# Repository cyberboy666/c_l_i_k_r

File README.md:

# c_l_i_k_r
a [r_e_c_u_r](https://github.com/cyberboy666/r_e_c_u_r) video sampler extension circuit - custom keypad & midi controller

- this circuit is distributed by __UNDERSCORES__ - _an open video hardware label_ : it is available to purchase - as a pcb, kit or assembled unit - at [underscores.shop](https://underscores.shop/c_l_i_k_r/)
- the schematic for the circuit can be found [here](/hardware/schematic.pdf)
- the pcb gerber files for the lastest version can be found [here](/hardware/gerber_latest.zip)
- interactive BOM is [here](https://htmlpreview.github.io/?https://github.com/cyberboy666/c_l_i_k_r/blob/main/hardware/bom/ibom.html)
- consider [donating](https://opencollective.com/underscores) to the underscores project to help us continue creating for the commons
## description

__NOTE__ : _c_l_i_k_r is an extension circuit for my existing raspberry pi project [r_e_c_u_r](https://github.com/cyberboy666/r_e_c_u_r) - although this circuit will function as a stand alone midi+keypad controller it is mainly intended to be used with r_e_c_u_r_

This is a custom controller designed to operate the rpi video instrument r_e_c_u_r. It uses an arduino pro-micro to send key-presses and midi values to the pi over usb

- 20x tac-switches for discrete control
- 4x knobs + 4x cv inputs for continuous control
- firmware can be configured to send midi messages or keyboard presses

## demo video

### background

this is an extension circuit that aims to offer an alternative to using cheapo plastic numpads to control recur. when i first designed recur i decided to use [these](https://www.aliexpress.com/item/4000748567192.html) numpads from aliexpress. my main goals at the time were making the project as simple and accessable as possible. however over the last few years many people have had problems using (possible variations?) of these numpads and others. seemingly similar devices run conflicting firmware, different layout of keys on different versions, crashes, gross hacks needed in the code, partial working units, and many more frustrating problems that are impossible for me to debug without owning every differnet device. i am also aware of contributing to the consumption of ecologically and ethically problematic products by endorsing these devices..

alsonow that recur has evolved beyond just a sample-player, having continuous control over parameters (like shaders) is more important than it was before. still one of the best options is to use a korg-nano-kontrol or similar midi controller as this gives many faders to control effects with. however for people who dont have a nanokontrol or want to use it elsewhere in their setup, i have been thinking of a small cheap and simple alterative to using numpads

# documentation

this project is fully _open-source hardware_ - all the files required to build it are included in this repo for free. if you have the time and/or skill you can contribute back by collaborating on / testing new designs, improving these docs, making demo videos/other creative content etc. you can also support the project financially by [donating directing](https://opencollective.com/underscores), or purchasing through the [web shop](https://underscores.shop).

depending on whether you are going fully diy or buying an assembled and tested unit, some of the following guides will be relavent to you. the flow would be:

## ordering parts

<details><summary><b>parts sourcing guide (w/ notes on pcb fabracation )</b> - start here if you are building fully from scatch or have purchased a pcb</summary>

i try to source all the parts i can from either:
- [tayda](https://www.taydaelectronics.com/) ; cheaper for common parts like resistors etc, also good for mechanical parts like switches and buttons
- [mouser](https://www.mouser.de/) ; has lots more options, speciality video ic's, can sometimes cost more (free shipping on orders over 50euros)
- other ; ocationally there will be parts which will need to be sourced elsewhere - usaully either aliexpress, ebay or amazon etc...

take a look at the [full_bom](/hardware/bom/full_bom.csv) for this project to see where i am sourcing each part from

since the only part on this BOM from mouser is the pots it may not be worth doing an order only for these - you could replace these with tayda pots `A-5531 or `A-1850` instead - if you are happy with the shorter shaft length.
  
## import into tayda

- go to the [tayda quick order](https://www.taydaelectronics.com/quick-order/) and in bottom corner choose _add from file_
- select the file [tayda_bom.csv](./hardware/bom/tayda_bom.csv) in the BOM folder (you will have to download it first or clone this repo)
- after importing select _add to cart_
- __NOTE:__ the minimum value for resistors is 10, so you may need to modify these values to add to cart (or if they are already modified here you will need to see the  full_bom for actual part QTY) 

- OPTIONAL: it is a good idea to add some dip-ic sockets and 2.54pin headers/sockets to your tayda order if you dont have them around already
  
## import into mouser

- go to [mouser bom tool](https://nz.mouser.com/Bom/) and click _upload spreadsheet_
- select the file [mouser_bom.csv](./hardware/bom/mouser_bom.csv) in this folder (you will have to download it first or clone this repo), then _upload my spreadsheet_ and _next_
- ensure that __Mouser Part Number__ is selected in the dropdown above the first row, then _next_, _process_
- if everything looks correct can now put _add to basket_

## selecting to omit some parts
  
- you may not want to include the 4x CV inputs in your build. in this case the 4x jacks, 4x resistors and 8x diode can be omitted from build
- you can also omit the 4x pots if you only want to use c_l_i_k_r as a usb-keyboard (for example if you already have a midi controller to use with r_e_c_u_r)
  
# ordering pcbs

you can support this project by buying individual pcbs from the [shop](https://underscores.shop). if you would rather have pcbs fabricated from gerbers directly the file you need is [here](/hardware/gerber_latest.zip) 

- i get my pcbs fabricated from [jlcpcb](https://cart.jlcpcb.com/quote) - 5 is the minumum order per design
- upload the zip file with the `add gerber file` button
- the default settings are mostly fine - set the __PCB Qty__ and __PCB Color__ settings (you can check that the file looks correct with pcb veiwer)
- it may be best to combine orders with other pcbs you want to have fab'd since the shipping can cost more than the items - also orginising group buys is a good way to distribute the extra pcbs /costs 
  
i often use jlcpcb because they are reliable, cheap and give you an option of colours. remember though that the cheapest Chinese fab houses are not always the most ethical or environmently friendly - if you can afford it consider supporting local companies. 

</details>

## assembly guide

<details><summary><b>assembly guide</b> - start here if you have purchased a diy kit</summary>

## interactive BOM for build guiding

follow this link to view the [interactive BOM](https://htmlpreview.github.io/?https://github.com/cyberboy666/c_l_i_k_r/blob/main/hardware/bom/ibom.html)

## general solder advices

- remember to heat pad first (2-3seconds), then add solder, then continue to heat (1-2seconds)

- Checkout the web-comic [soldering is easy](https://mightyohm.com/files/soldercomic/FullSolderComic_EN.pdf) for more soldering advice

## general order of assembly

- in general while assembling i start placing resistors and capacitors first. placing 5 - 10 components at a time and then flipping the board to solder them and trim the legs etc.
- next i would do diodes, transistors and ic's - taking care that these are placed in the right direction (using a ic socket can be useful)
- finally i place the interface parts - rca jacks, power jack, pots and switches - make sure these have lots of solder on for structural stablity

## specific assembly advice

- start with the lowest to place components : resistors and diodes, then do the tact buttons

- if you want to be able to remove the pro-micro from the board you will need to solder header sockets to the board – otherwise can directly solder pro-micro header pins

- finally place and solder the pots and jacks.
  
</details>
  
## firmware guide

<details><summary><b>firmware guide</b> - for editing the code & flashing it to your micro-controller</summary>
  
## flashing firmware onto the micro-controller
  
if you have got a kit from the shop the default firmware will be pre-configured - still you probably will want to follow this so you can edit the code and update the mappings.
  
### install guide
  
all _underscores_ projects with micro-controllers use [platformio](https://platformio.org/) with [visual studio code](https://code.visualstudio.com/) to edit, flash and monitor the code.
  
- first download (and unzip) the code in this repo - easiest is [as a zip](https://github.com/cyberboy666/c_l_i_k_r/archive/refs/heads/main.zip) or you can clone using git if you are comfortable with this
- next download, install and open [visual studio code](https://code.visualstudio.com/#alt-downloads)
- now open the extension tab within vscode on left vertical menu (or press ctrl-shift-x) and search for `platformio` to install this extension

- connect the micro-controller to computer via usb, open the c_l_i_k_r software folder (ctrl-k ctrl-o) in vscode and find the _platformio_ commands (either in left vertical menu under _platformio_ or little tick/arrow symbols along bottom blue bar) - `PlatformIO: Upload` should flash the default code to your micro-controller

### mapping edit guide
  
coming soon
  
</details>
  
## operating guide
  
<details><summary><b>operating guide</b> - start here if you have purchased an assembled unit</summary>

By connecting _c_l_i_k_r_ to _r_e_c_u_r_ with a usb cable the pi should auto-detect it as a usb-keyboard – as with any recur controls you will need to connect the keyboard before booting to ensure key mapping is performed on boot.

If `MIDI_INPUT` is set to `usb` under the _r_e_c_u_r_ __user_input__ setting then it should auto-detect it as usb-midi-controller also.

If you wish to instead connect a different midi device while using _c_l_i_k_r_ as a keyboard try the `CYCLE_MIDI_PORT` action in __user_input__ settings

The default mapping outputs `channel0: cc0 – cc3` on the 4 knobs and cv inputs of _c_l_i_k_r_ – this can be customised by editing the _c_l_i_k_r_ firmware. Tact buttons do not send midi by default but this can be enabled also in the firmware

one thing to note is that the _c_l_i_k_r_ keyboard only sends _key_press_ commands, not any _key_release_ commands - for this reason "gated" presses will not work - if your __FN__ key is not working with c_l_i_k_r then make sure that __SETTINGS -> sampler -> FUNC_GATED == off__ (same for ACTION_GATED)

[sending key_release commands may be possible in a future firmware updates so let me know if this is important to you ! ]

## flashing firmware to micro-controller

if you have got a kit from the shop the default firmware will be pre-configured - still you can follow this guide so you can edit the code and update the firmware.
  
### install guide
  
all _underscores_ projects with micro-controllers use [platformio](https://platformio.org/) with [visual studio code](https://code.visualstudio.com/) to edit, flash and monitor the code.
  
- first download (and unzip) the code in this repo - easiest is [as a zip](https://github.com/cyberboy666/c_l_i_k_r/archive/refs/heads/main.zip) or you can clone using git if you are comfortable with this
- next download, install and open [visual studio code](https://code.visualstudio.com/#alt-downloads)
- now open the extension tab within vscode on left vertical menu (or press ctrl-shift-x) and search for `platformio` to install this extension

- connect the micro-controller to computer via usb, open the c_l_i_k_r software folder (ctrl-k ctrl-o) in vscode and find the _platformio_ commands (either in left vertical menu under _platformio_ or little tick/arrow symbols along bottom blue bar) - `PlatformIO: Upload` should flash the default code to your micro-controller

</details>

### more info

<details><summary><b>how the circuit works</b></summary>
  
[coming soon]
                                                                                                                             
</details>

<details><summary><b>contributing guide</b></summary>
  
if you would like to contribute back to these projects in some way but dont know how the best thing (for now) would be to reach out to me directly ( tim@cyberboy666.com or @cyberboy666 on scanlines forum) - i will be happy to help
  
</details>

## credits & more info

This circuit is distributed through UNDERSCORES – open video hardware label – visit [underscores.shop](https://underscores.shop) for more info

The pcb was designed using KICAD

Everything from gerbers, cad files, panels and documentation is freely available online and distributed under CC-BY-SA / open-source licenses – help us contribute to the commons !

Ask any questions or start discussions related to this project on the [scanlines.xyz](https://scanlines.xyz) forum – an online community space dedicated to diy av / electronic media art

You can contact me directly at tim (at) cyberboy666 (dot) com 
Please get in touch if you are interested in hosting a workshop !

Thanks to all the r_e_c_u_r users who inspire me to better this project! to Bastien Lavaud for circuit advice, always. To Ben Caldwell for project advice. To everyone who has or will contribute ♥♥♥

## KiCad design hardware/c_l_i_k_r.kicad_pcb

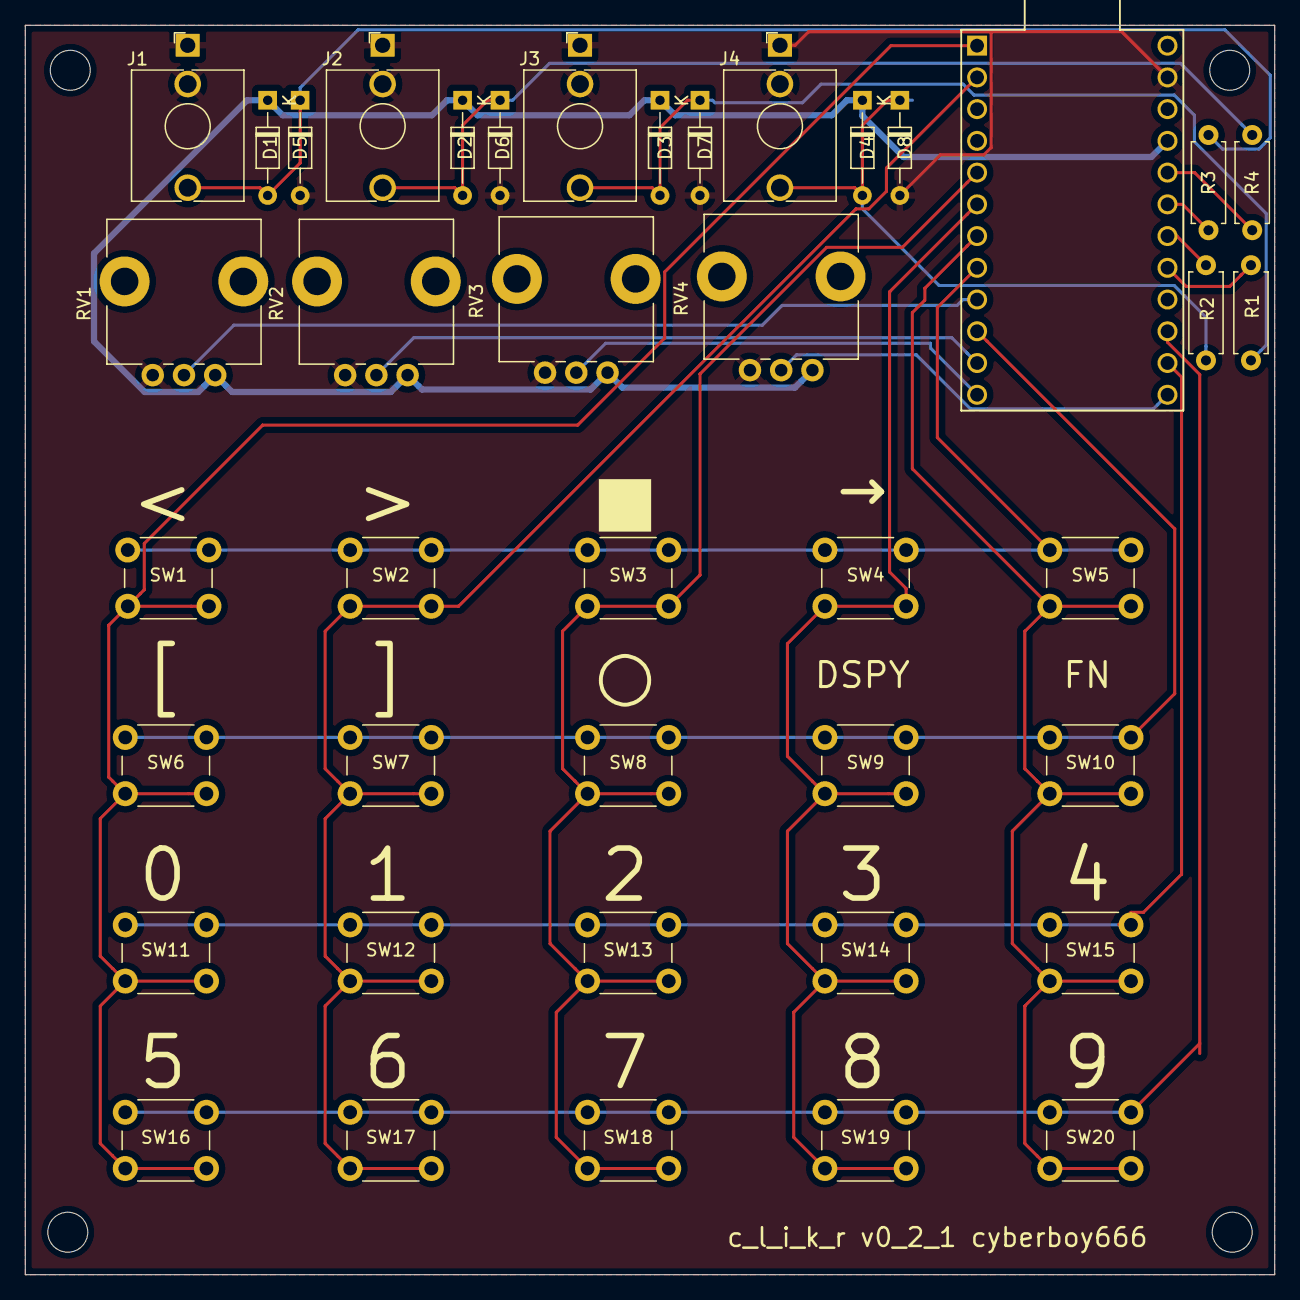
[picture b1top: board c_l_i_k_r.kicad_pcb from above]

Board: 2 copper layers, 100.0 x 100.0 mm, 41 parts (0 on the bottom side), 23 nets.

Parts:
D1, D2, D3, D4, D5, D6, D7, D8: bat46; D_DO-34_SOD68_P7.62mm_Horizontal
J1, J2, J3, J4: mono_jack_3.5mm; Jack_3.5mm_QingPu_WQP-PJ398SM_Vertical_CircularHoles
R1, R2, R3, R4: 1k; R_Axial_DIN0207_L6.3mm_D2.5mm_P7.62mm_Horizontal
RV1, RV2, RV3, RV4: 10k_pot; Potentiometer_Alps_RK09L_Single_Vertical
SW1, SW2, SW3, SW4, SW5, SW6, SW7, SW8, SW9, SW10, SW11, SW12, SW13, SW14, SW15, SW16, SW17, SW18, SW19, SW20: Push; SW_PUSH_6mm_H7.3mm
U1: ProMicro

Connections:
+5V: D1.1, D2.1, D3.1, D4.1, RV1.1, RV2.1, RV3.1, RV4.1, U1.21
GND: D5.2, D6.2, D7.2, D8.2, J1.S, J1.TN, J2.S, J2.TN, J3.S, J3.TN, J4.S, J4.TN, RV1.3, RV2.3, RV3.3, RV4.3, U1.23
unnamed: D1.2, D5.1, J1.T, R3.2
unnamed: D2.2, D6.1, J2.T, R4.2
unnamed: D3.2, D7.1, J3.T, R1.2
unnamed: D4.2, D8.1, J4.T, R2.2
analog_0: RV1.2, U1.9
analog_1: RV2.2, U1.11
analog_2: RV3.2, U1.12
analog_3: RV4.2, U1.13
analog_4: R1.1, U1.17
analog_5: R2.1, U1.18
analog_6: R3.1, U1.19
analog_7: R4.1, U1.20
key_x0: SW1.2, SW6.2, SW11.2, SW16.2, U1.1
key_x1: SW2.2, SW7.2, SW12.2, SW17.2, U1.2
key_x2: SW3.2, SW8.2, SW13.2, SW18.2, U1.5
key_x3: SW4.2, SW9.2, SW14.2, SW19.2, U1.6
key_x4: SW5.2, SW10.2, SW15.2, SW20.2, U1.7
key_y0: SW1.1, SW2.1, SW3.1, SW4.1, SW5.1, U1.8
key_y1: SW6.1, SW7.1, SW8.1, SW9.1, SW10.1, U1.10
key_y2: SW11.1, SW12.1, SW13.1, SW14.1, SW15.1, U1.14
key_y3: SW16.1, SW17.1, SW18.1, SW19.1, SW20.1, U1.15

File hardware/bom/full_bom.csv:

sku,qty,ref,val,vendor
A-1095,8,D1 D2 D3 D4 D5 D6 D7 D8 ,bat46,tayda
A-2563,4,J1 J2 J3 J4 ,mono_jack_3.5mm,tayda
A-2200,4,R1 R2 R3 R4 ,1k,tayda
A-5531,4,RV1 RV2 RV3 RV4 ,10k_pot,tayda
A-5129,20,SW1 SW2 SW3 SW4 SW5 SW6 SW7 SW8 SW9 SW10 SW11 SW12 SW13 SW14 SW15 SW16 SW17 SW18 SW19 SW20 ,Push,tayda
-,1,U1 ,ProMicro

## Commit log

2022-01-10 migrate to own repo
2022-02-22 update code and circuit revision
2022-02-22 rename kicad project
2022-02-28 update bom
2022-10-27 made pot holes larger
2022-10-28 fix lag problem
2022-11-01 update booklet
2023-07-25 add project dependancy
2024-05-19 add git attributes
